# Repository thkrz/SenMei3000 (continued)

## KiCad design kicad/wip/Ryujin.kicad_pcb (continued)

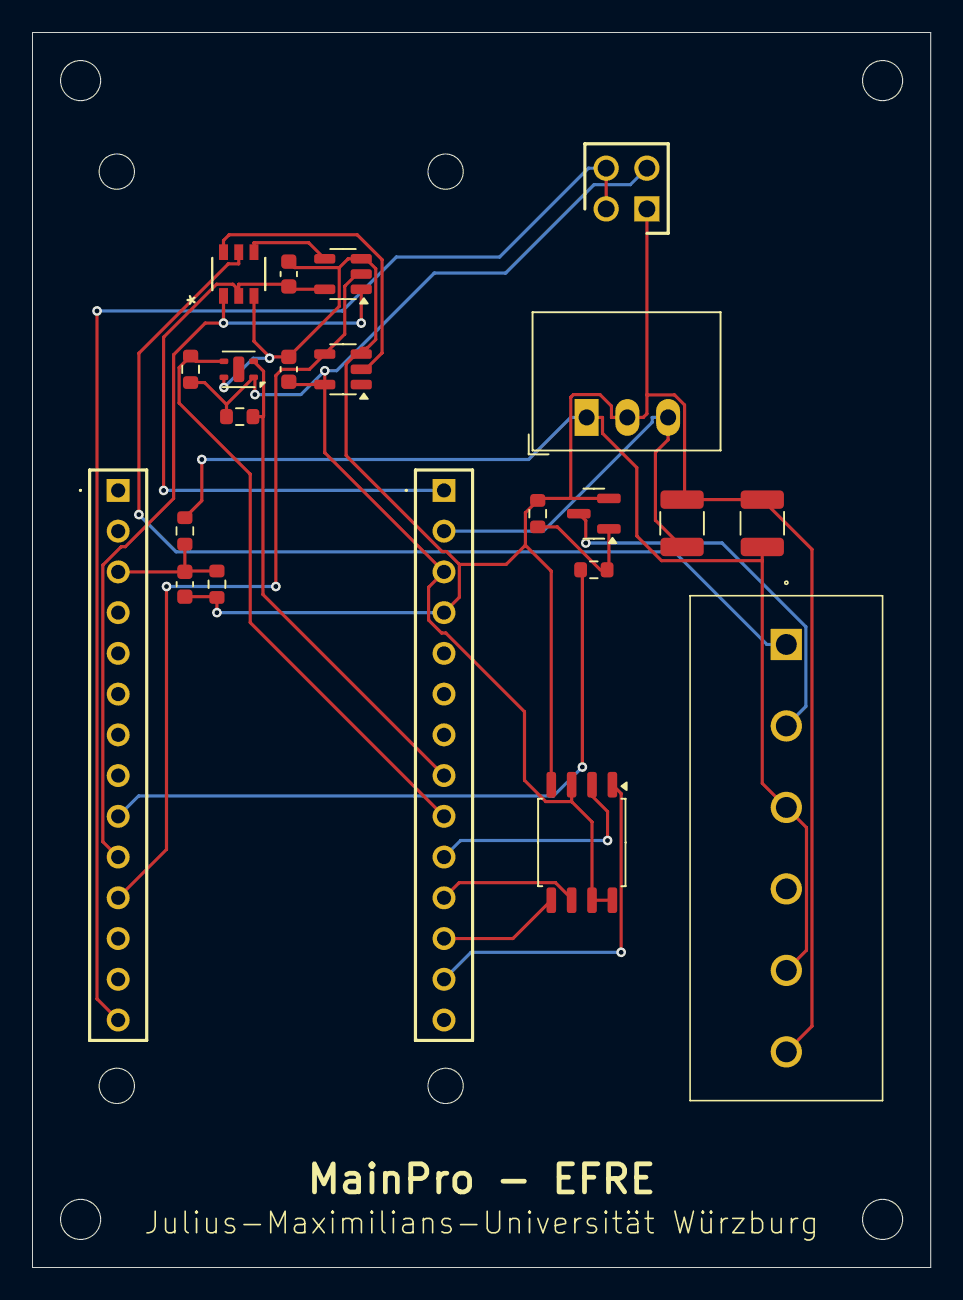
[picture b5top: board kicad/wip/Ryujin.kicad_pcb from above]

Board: 2 copper layers, 56.0 x 77.0 mm, 27 parts (0 on the bottom side), 21 nets.

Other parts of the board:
A1: Arduino_MKR_NB_1500_Socket; Arduino_MKR_NB_1500_Margin
H1, H2, H3, H4: MountingHole_2.5mm

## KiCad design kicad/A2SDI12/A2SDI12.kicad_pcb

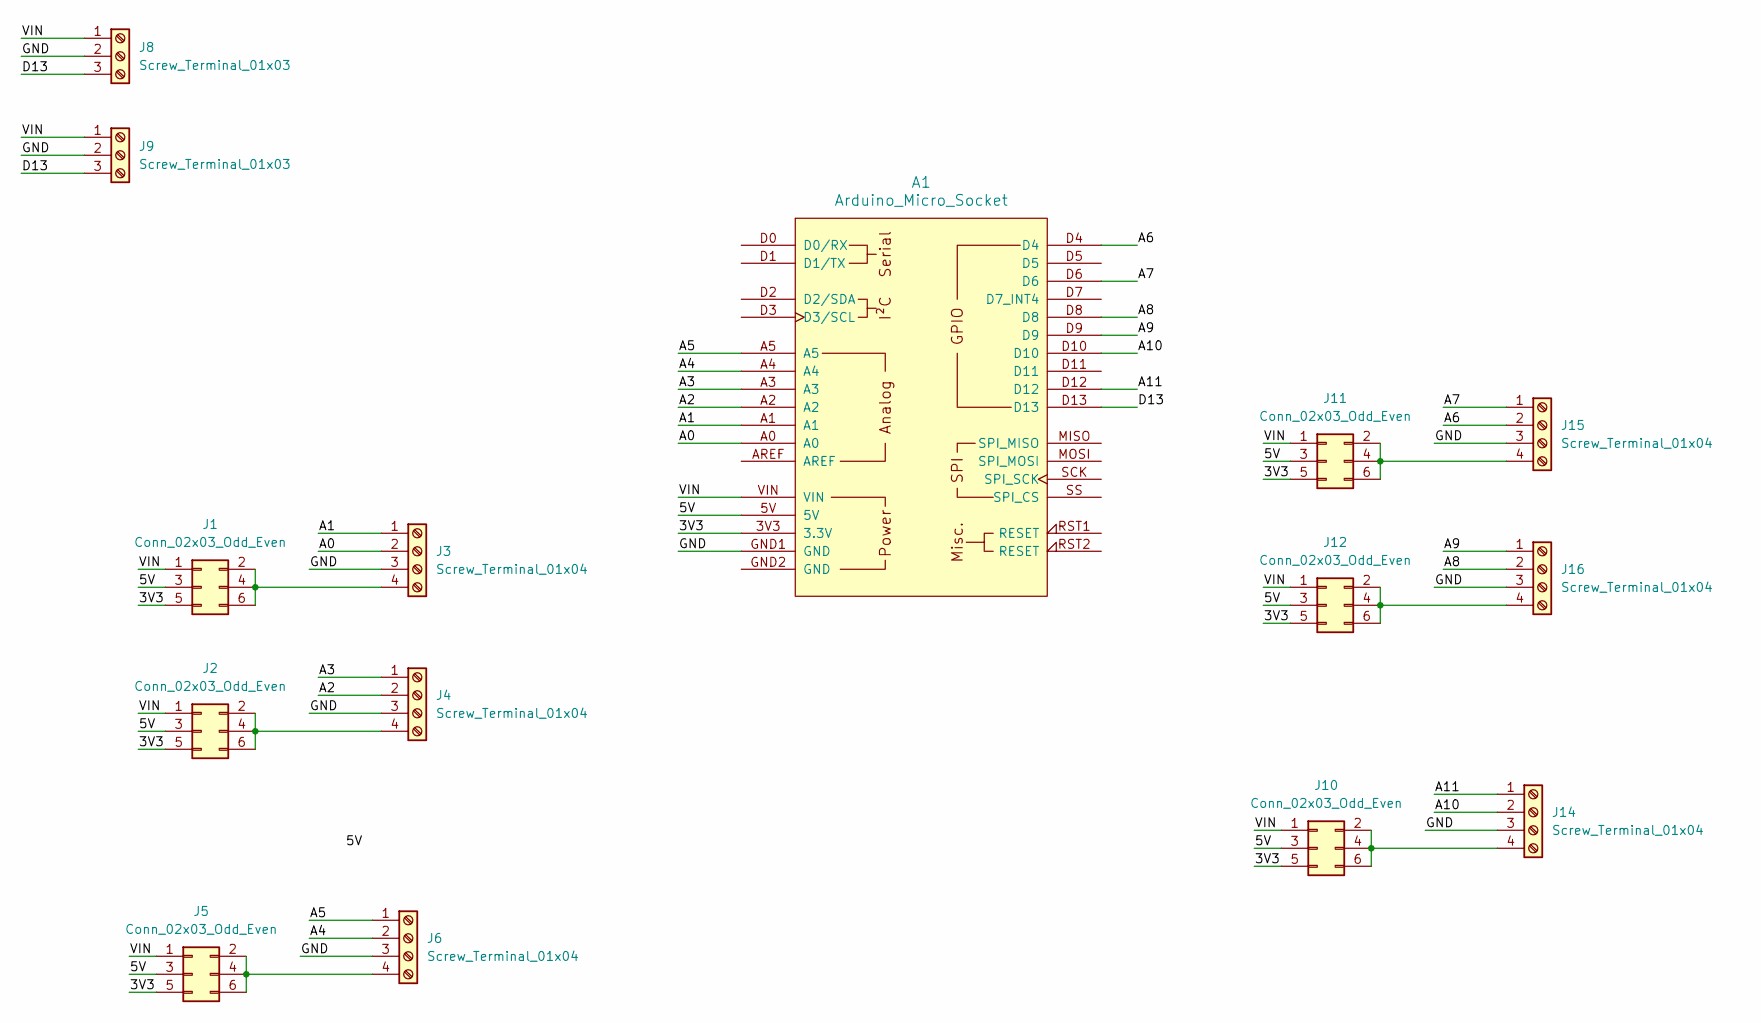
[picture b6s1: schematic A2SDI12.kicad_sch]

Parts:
A1: Arduino_Micro_Socket
J1, J2, J5, J10, J11, J12: Conn_02x03_Odd_Even; PinHeader_2x03_P2.54mm_Vertical
J3, J4, J6, J14, J15, J16: Screw_Terminal_01x04; TerminalBlock_Phoenix_MKDS-1,5-4-5.08_1x04_P5.08mm_Horizont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
J8, J9: Screw_Terminal_01x03; TerminalBlock_Phoenix_MKDS-1,5-3-5.08_1x03_P5.08mm_Horizont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

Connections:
/3V3: A1.3V3 (3.3V), J1.5, J2.5, J5.5, J10.5, J11.5, J12.5
/5V: A1.5V, J1.3, J2.3, J5.3, J10.3, J11.3, J12.3
/A0: A1.A0, J3.2
/A1: A1.A1, J3.1
/A2: A1.A2, J4.2
/A3: A1.A3, J4.1
/A4: A1.A4, J6.2
/A5: A1.A5, J6.1
/A6: A1.D4, J15.2
/A7: A1.D6, J15.1
/A8: A1.D8, J16.2
/A9: A1.D9, J16.1
/A10: A1.D10, J14.2
/A11: A1.D12, J14.1
/D0: A1.D0 (D0/RX)
/D1: A1.D1 (D1/TX)
/D13: A1.D13, J8.3, J9.3
/GND: A1.GND1 (GND), J3.3, J4.3, J6.3, J8.2, J9.2, J14.3, J15.3, J16.3
/VIN: A1.VIN, J1.1, J2.1, J5.1, J8.1, J9.1, J10.1, J11.1, J12.1
unnamed: J1.2, J1.4, J1.6, J3.4
unnamed: J2.2, J2.4, J2.6, J4.4
unnamed: J5.2, J5.4, J5.6, J6.4
unnamed: J10.2, J10.4, J10.6, J14.4
unnamed: J11.2, J11.4, J11.6, J15.4
unnamed: J12.2, J12.4, J12.6, J16.4

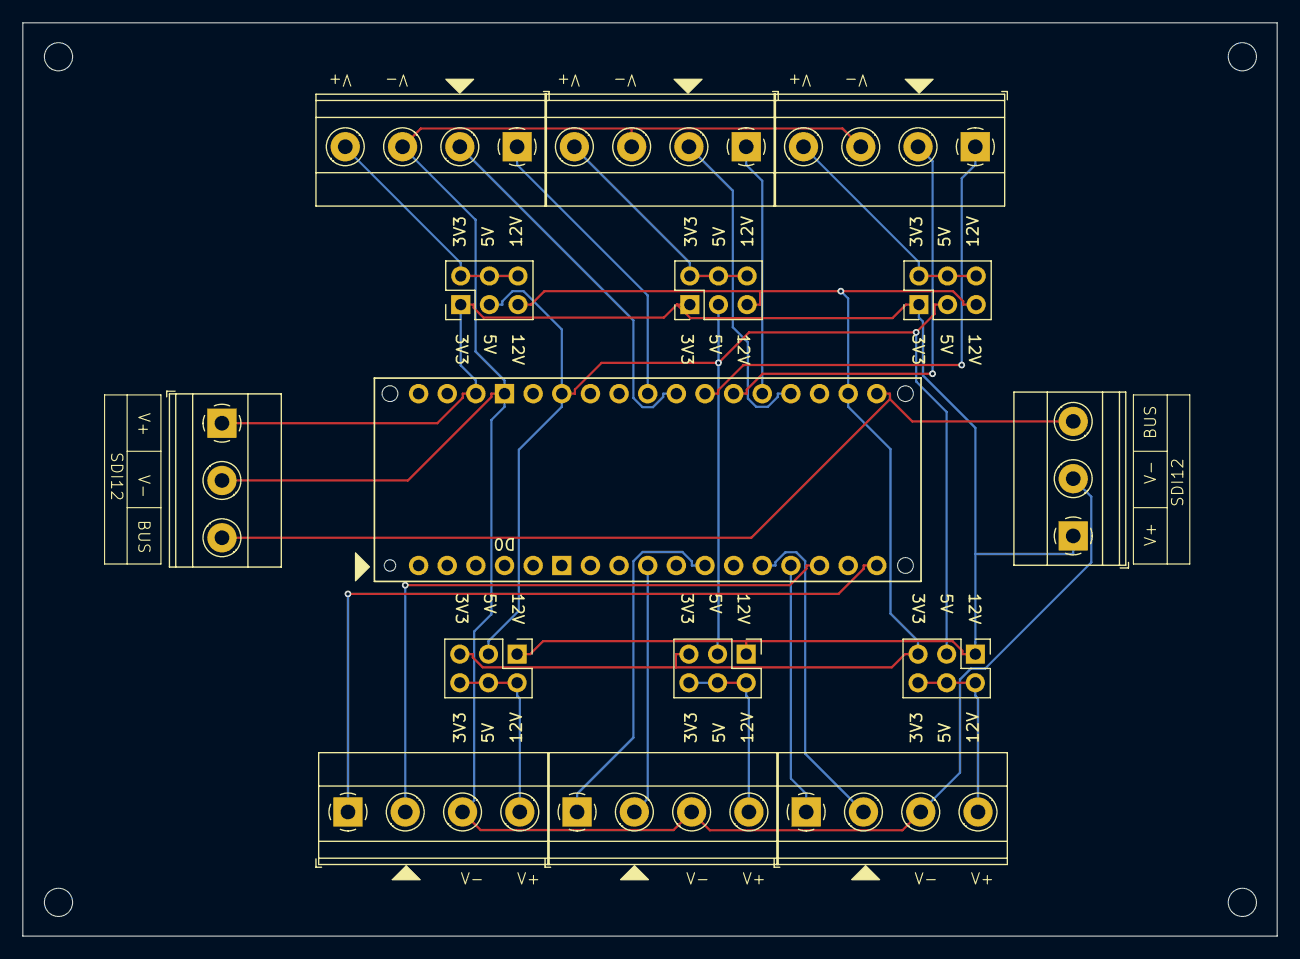
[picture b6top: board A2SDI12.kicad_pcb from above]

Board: 2 copper layers, 111.2 x 81.0 mm, 19 parts (0 on the bottom side), 23 nets.

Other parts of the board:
H1, H2, H3, H4: MountingHole_2.5mm

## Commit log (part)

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2025-01-29 Promises
2025-01-29 Encounter
2025-01-30 King for a Day
2025-01-30 When a Man Loves a Woman
2025-01-31 Protean Challenge
2025-01-31 The Wedding of Alcmene
2025-01-31 The Power
2025-01-31 Centaur Mentor Journey
2025-01-31 Judgment Day
2025-02-01 The Lost City
2025-02-02 Les Contemptibles
2025-02-02 Reign of Terror
2025-02-02 The End of the Beginning
2025-02-03 The Cave of Echoes
2025-02-03 Mercenary
2025-02-03 War Bride
2025-02-04 Doomsday
2025-02-04 Love Takes a Holiday
2025-02-04 Mummy Dearest
2025-02-04 A Rock and a Hard Place
2025-02-04 Atlantis
2025-02-04 Beanstalks and Bad Eggs
2025-02-05 Not Fade Away
2025-02-05 Monster Child in the Promised Land
2025-02-05 The Green-Eyed Monster
2025-02-05 Prince Hercules
2025-02-05 A Star to Guide Them
2025-02-05 Hero's Heart
2025-02-06 The Lady and the Dragon
2025-02-06 Long Live the King
2025-02-07 Surprise
2025-02-07 Regrets… I've Had a Few
2025-02-07 Web of Desire
2025-02-07 Stranger in a Strange World
2025-02-08 Two Men and a Baby
2025-02-08 Prodigal Sister
2025-02-08 ...and Fancy Free
2025-02-09 If I Had a Hammer
2025-02-10 Hercules on Trial
2025-02-10 Medea Culpa
2025-02-10 Men in Pink
2025-02-11 Armageddon Now: Part 1
2025-02-12 Armageddon Now: Part 2
2025-02-12 Yes, Virginia, There Is a Hercules
2025-02-13 Porkules
2025-02-13 One Fowl Day
2025-02-14 My Fair Cupcake
2025-02-14 War Wounds
2025-02-16 Twilight
2025-02-16 Top God
2025-02-16 Reunions
2025-02-17 Faith
2025-02-18 Descent
2025-02-18 Resurrection
2025-02-18 Genies and Grecians and Geeks, Oh My
2025-02-18 Render Unto Caesar
2025-02-19 Norse by Norsevest
2025-02-19 Somewhere Over the Rainbow Bridge
2025-02-20 Darkness Rising
2025-02-20 For Those of You Just Joining Us
2025-02-20 Let There Be Light
2025-02-22 Redemption
2025-02-22 Sky High
2025-02-22 Stranger and Stranger
2025-02-22 Just Passing Through
2025-02-22 Greece Is Burning
2025-02-23 We'll Always Have Cyprus
2025-02-23 The Academy
2025-02-24 Love on the Rocks
2025-02-24 Once Upon a Future King
2025-02-24 Fade Out
2025-02-25 My Best Girl's Wedding
2025-02-26 Revelations
2025-02-26 Be Deviled
2025-02-26 Love, Amazon Style
2025-02-26 Rebel with a Cause
2025-02-26 Darkness Visible
2025-02-26 Hercules, Tramps & Thieves
2025-02-27 City of the Dead
2025-02-27 A Wicked Good Time
2025-02-28 Full Circle
2025-02-28 Sins of the Past
2025-02-28 Chariots of War
2025-03-01 Dreamworker
2025-03-02 Cradle of Hope
2025-03-02 The Path Not Taken
2025-03-03 The Reckoning
2025-03-03 The Titans
2025-03-04 Prometheus
2025-03-04 Death in Chains
2025-03-05 Hooves & Harlots
2025-03-05 The Black Wolf
2025-03-06 Beware Greeks Bearing Gifts
2025-03-06 Athens City Academy of the Performing Bards
2025-03-07 A Fistful of Dinars
2025-03-07 Warrior... Princess
2025-03-08 Mortal Beloved
2025-03-09 The Royal Couple of Thieves
2025-03-09 The Prodigal
2025-03-09 Altared States
2025-03-09 Ties That Bind
2025-03-09 The Greater Good
2025-03-09 Callisto
2025-03-09 Death Mask
2025-03-09 Is There a Doctor in the House?
2025-03-09 Orphan of War
2025-03-10 Remember Nothing
2025-03-11 The Giant Killer
2025-03-11 Girls Just Wanna Have Fun
2025-03-12 Return of Callisto
2025-03-13 Warrior... Princess... Tramp
2025-03-13 Intimate Stranger
2025-03-14 Ten Little Warlords
2025-03-14 A Solstice Carol
2025-03-15 The Xena Scrolls
2025-03-15 Here She Comes... Miss Amphipolis
2025-03-15 Destiny
2025-03-15 The Quest
2025-03-15 A Necessary Evil
2025-03-15 A Day in the Life
2025-03-16 For Him the Bell Tolls
2025-03-16 The Execution
2025-03-16 Blind Faith
2025-03-16 Ulysses
2025-03-16 The Price
2025-03-17 Lost Mariner
2025-03-17 A Comedy of Eros
2025-03-17 The Furies
2025-03-17 Been There, Done That
2025-03-18 The Dirty Half Dozen
2025-03-18 The Deliverer
2025-03-19 Gabrielle's Hope
2025-03-19 The Debt, Part 1
2025-03-19 The Debt, Part 2
2025-03-20 The King of Assassins
2025-03-20 Warrior… Priestess… Tramp
2025-03-21 The Quill Is Mightier…
2025-03-21 Maternal Instincts
2025-03-22 The Bitter Suite
2025-03-22 One Against an Army
2025-03-23 Forgiven
2025-03-23 King Con
2025-03-23 When in Rome...
2025-03-23 Forget Me Not
2025-03-24 Fins, Femmes and Gems
2025-03-25 Tsunami
2025-03-26 Vanishing Act
2025-04-04 Sacrifice, Part 1
2025-05-06 Sacrifice, Part 2
2025-05-06 Adventures in the Sin Trade, Part 1
2025-05-08 Adventures in the Sin Trade, Part 2
2025-05-08 A Family Affair
2025-05-14 In Sickness and in Hell
2025-05-14 A Good Day
2025-05-15 A Tale of Two Muses
2025-05-15 Locked up and Tied Down
2025-05-15 Crusader
2025-05-15 Past Imperfect
2025-05-15 The Key to the Kingdom
2025-05-15 Daughter of Pomira
2025-05-16 If the Shoe Fits...
2025-05-16 Paradise Found
2025-05-17 Devi
2025-05-29 Between the Lines
2025-05-29 The Way
2025-06-02 The Play's the Thing
2025-06-02 The Convert
2025-06-02 Takes One to Know One
2025-06-02 Endgame
2025-06-08 The Ides of March
2025-06-09 Déjà Vu All over Again
2025-06-13 Fallen Angel
2025-08-20 Chakram
2025-08-20 Succession
2025-08-21 Animal Attraction
2025-08-21 Them Bones, Them Bones
2025-08-22 Purity
2025-08-25 Back in the Bottle
2025-08-25 Little Problems
2025-08-25 Seeds of Faith
2025-08-25 Lyre, Lyre, Hearts on Fire
2025-08-25 Punch Lines
2025-08-27 God Fearing Child
2025-08-27 Eternal Bonds
2025-08-27 Amphipolis under Siege
2025-09-01 Married with Fishsticks
2025-09-02 Lifeblood
2025-09-03 Kindred Spirits
2025-09-03 Antony and Cleopatra
2025-09-03 Looking Death in the Eye
2025-09-03 Livia
2025-09-04 Motherhood
2025-09-04 Coming Home
2025-09-04 The Haunting of Amphipolis
2025-09-04 Heart of Darkness
2025-09-04 Who's Gurkhan?
2025-09-04 Legacy
2025-09-04 The Abyss
2025-09-05 The Rheingold
2025-09-05 The Ring
2025-09-05 Return of the Valkyrie
2025-09-06 Old Ares had a Farm
2025-09-06 Dangerous Prey
2025-09-06 The God you Know
2025-09-06 You Are There
2025-09-07 Path of Vengeance
2025-09-07 To Helicon and Back
2025-09-07 Send in the Clones
2025-09-07 The Last of the Centaurs
2025-09-08 When Fates Collide
2025-09-08 Many Happy Returns
2025-09-12 Aktualisieren von W25QLOG.cpp
2025-09-12 Soul Possession
2025-09-12 A Friend in Need, Part 1
2025-09-12 A Friend in Need, Part 2
2025-09-12 To Be Or Not To Be
2025-09-12 The Devil's Window
2025-09-13 Treasure of The Mind
2025-09-13 Games
2025-09-13 Treasures of the Tonga Trench
2025-09-14 Clean up
2025-09-14 Brothers and Sisters
2025-09-14 Aktualisieren von gps.cpp
2025-09-16 Give Me Liberté
2025-09-17 Knight of Shadows
2025-09-17 Bad Water
2025-09-17 The Regulator
2025-09-18 The Wrong Path
2025-09-18 Eye of the Beholder
2025-09-19 The Road to Calydon
2025-09-19 The Festival of Dionysus
2025-09-19 Ares
2025-09-19 As Darkness Falls
2025-09-20 GSM Test
2025-09-20 Format
2025-09-20 New tool
2025-09-20 New sel
